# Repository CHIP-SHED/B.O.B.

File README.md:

Add battery power and LiPo charging to your Raspberry Pi projects.

======

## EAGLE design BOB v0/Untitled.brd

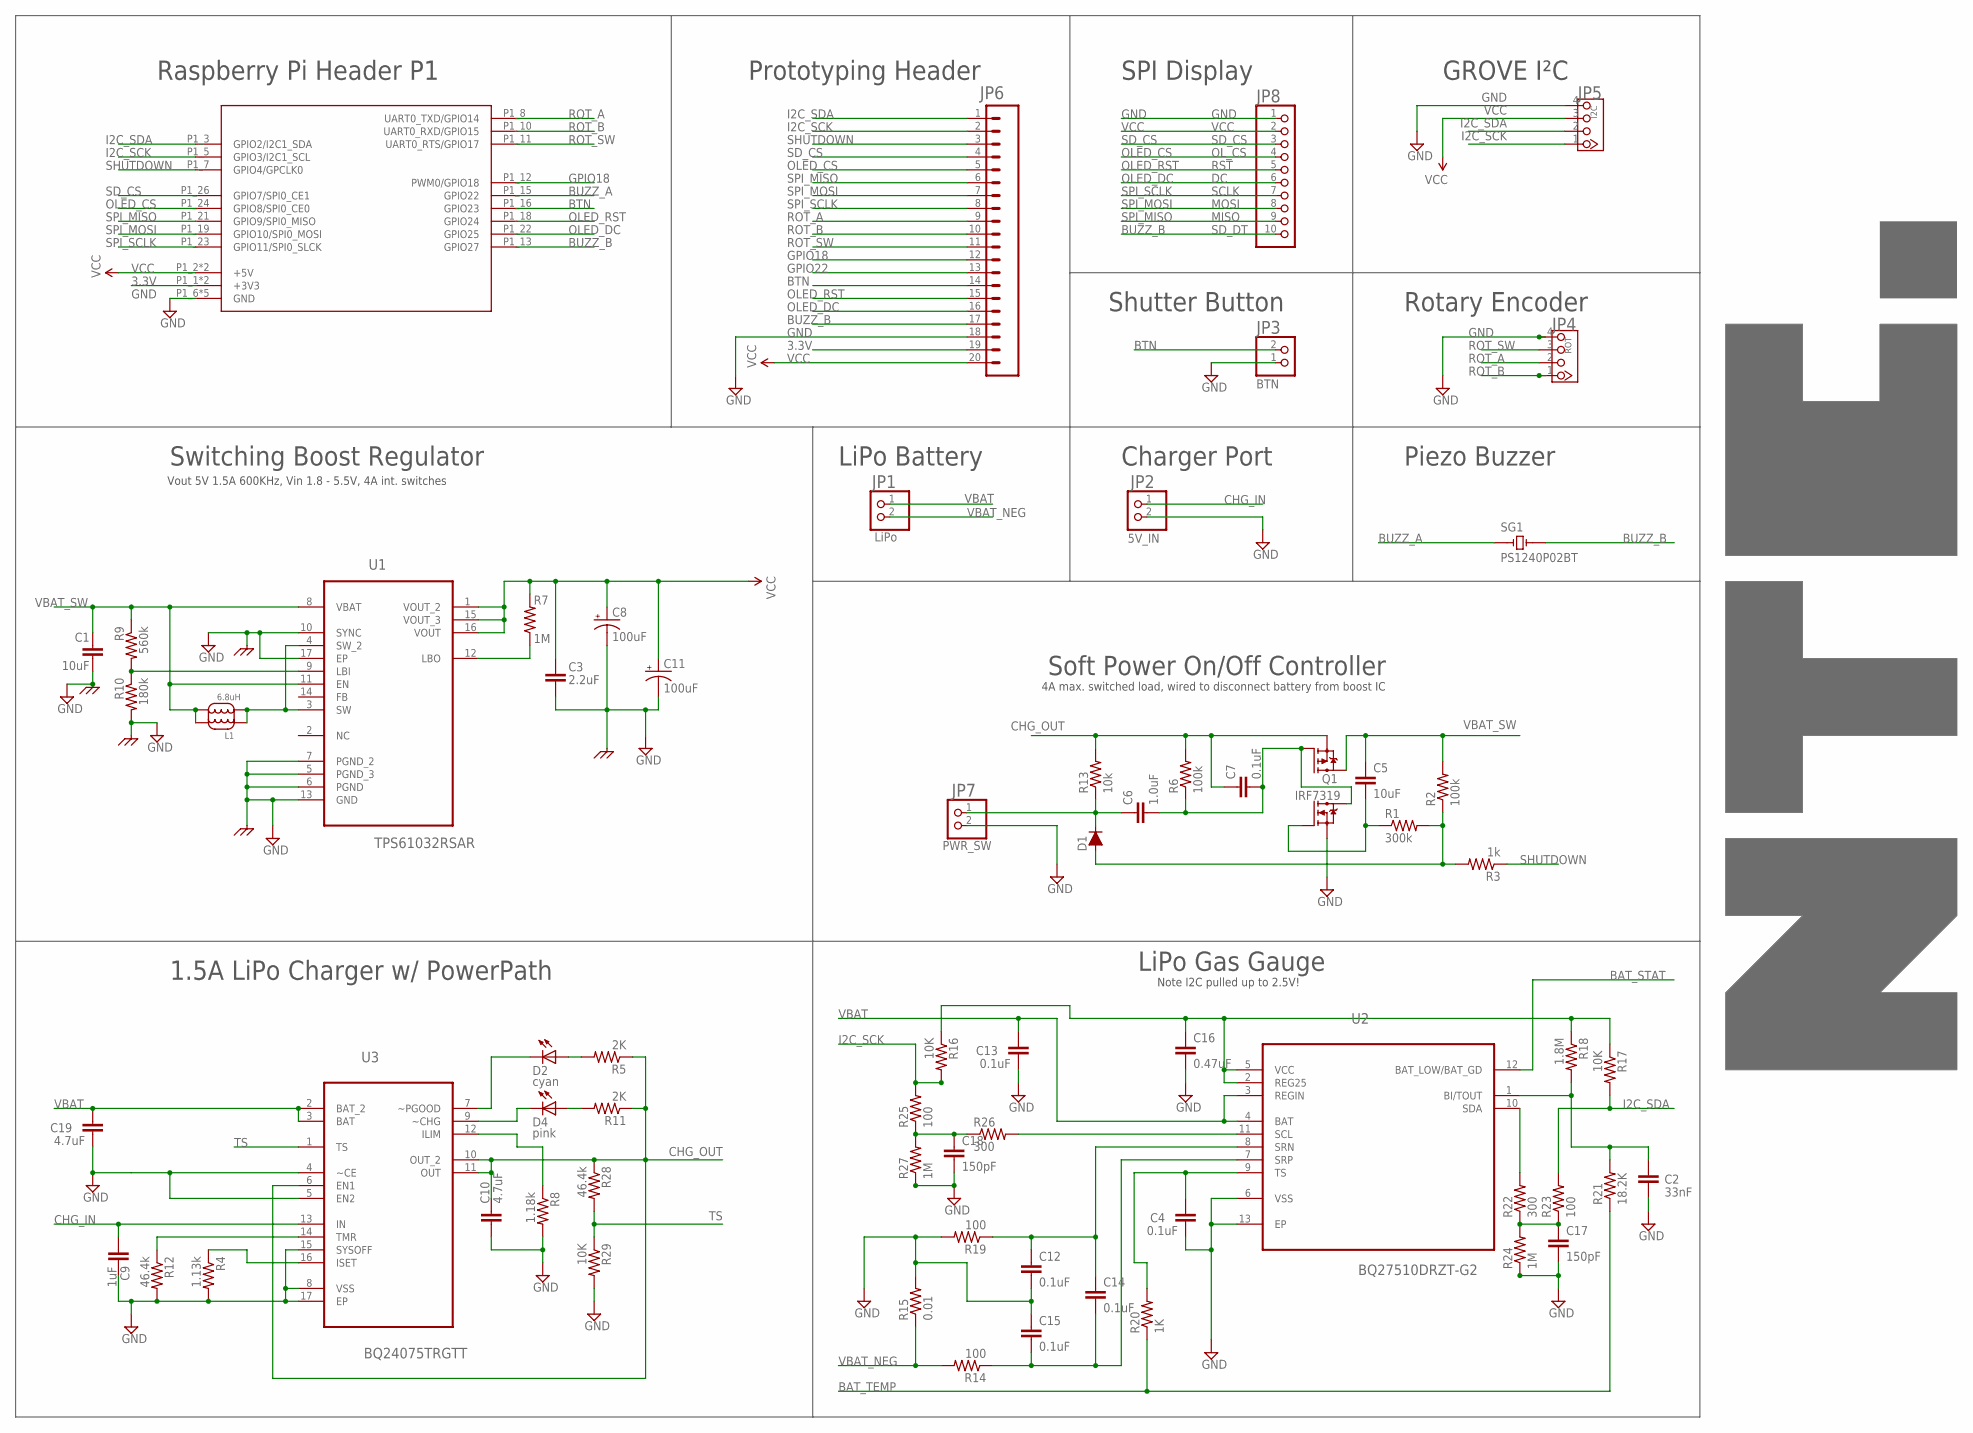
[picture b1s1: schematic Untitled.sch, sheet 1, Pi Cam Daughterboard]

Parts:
C1: 10uF; 1206
C2: 33nF; 0603-CAP
C3: 2.2uF; 0603
C4, C7, C12, C13, C14, C15: 0.1uF; 0603-CAP
C5: 10uF; 0603-CAP
C6: 1.0uF; 0603-CAP
C8, C11: 100uF; EIA3216
C9: 1uF; 0603-CAP
C10, C19: 4.7uF; 0603-CAP
C16: 0.47uF; 0603-CAP
C17, C18: 150pF; 0603-CAP
D1: D-FILL-SMB; SMB
D2: cyan; LED-0603
D4: pink; LED-0603
JP1: LiPo; JST-PH-2-THM-RA
JP2: 5V_IN; JST-PH-2-THM-RA
JP3: BTN; JST-PH-2-THM-RA
JP4: ROT; CONNECTOR_4P-2.0-90D
JP5: I2C; CONNECTOR_4P-2.0-90D
JP6: M20LOCK_LONGPADS; 1X20_LOCK_LONGPADS
JP7: PWR_SW; JST-PH-2-THM-RA
JP8: PINHD-1X10; 1X10-BIG
L1: 6.8uH; SUMIDA_CDRH124
PICAM_SHIELD: PICAM_RPI-B-PICAM
Q1: IRF7319; SO08-IRF
R1: 300k; 0603-RES
R2, R6: 100k; 0603-RES
R3: 1k; 0603-RES
R4: 1.13k; 0603-RES
R5, R11: 2K; 0603-RES
R7: 1M; 0603-RES
R8: 1.18k; 0603-RES
R9: 560k; 0603-RES
R10: 180k; 0603-RES
R12, R28: 46.4k; 0603-RES
R13: 10k; 0603-RES
R14, R19: 100; 0603-RES
R15: 0.01; SPARKFUN_1206
R16, R17, R29: 10K; 0603-RES
R18: 1.8M; 0603-RES
R20: 1K; SPARKFUN_1206
R21: 18.2K; SPARKFUN_1206
R22, R26: 300; SPARKFUN_1206
R23, R25: 100; SPARKFUN_1206
R24, R27: 1M; SPARKFUN_1206
SG1: PS1240P02BT; PS1240
U1: TPS61032RSAR; QFN65P400X400X100-17N
U2: BQ27510DRZT-G2; SON40P400X250X100-13N
U3: BQ24075TRGTT; QFN50P300X300X100-17N

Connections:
3.3V: JP6.19, PICAM_SHIELD.P1_1 (+3V3), PICAM_SHIELD.P1_17 (+3V3)
BAT_STAT: U2.12 (BAT_LOW/BAT_GD)
BAT_TEMP: R20.1, R21.1
BTN: JP3.2 (1), JP6.14, PICAM_SHIELD.P1_16 (GPIO23)
BUZZ_A: PICAM_SHIELD.P1_15 (GPIO22), SG1.P$1 (1)
BUZZ_B: JP6.17, JP8.10, PICAM_SHIELD.P1_13 (GPIO27), SG1.P$2 (2)
CHG_IN: C9.1, JP2.1 (2), U3.13 (IN)
CHG_OUT: C7.1, C10.1, Q1.3 (P-S2), R5.1, R6.2, R11.1, R13.2, R28.1, U3.6 (EN1), U3.10 (OUT_2), U3.11 (OUT)
GND: C1.2, C2.2, C3.2, C4.2, C8.C (-), C9.2, C10.2, C11.C (-), C12.2, C13.2, C15.1, C16.2, C17.2, C18.2, C19.2, JP2.2 (1), JP3.1 (2), JP4.4, JP5.4, JP6.18, JP7.2 (1), JP8.1, PICAM_SHIELD.P1_6 (GND), PICAM_SHIELD.P1_9 (GND), PICAM_SHIELD.P1_14 (GND), PICAM_SHIELD.P1_20 (GND), PICAM_SHIELD.P1_25 (GND), Q1.1 (N-S1), R4.2, R8.2, R10.2, R12.2, R15.2, R19.2, R24.1, R27.1, R29.2, U1.5 (PGND_3), U1.6 (PGND), U1.7 (PGND_2), U1.10 (SYNC), U1.13 (GND), U1.17 (EP), U2.6 (VSS), U2.13 (EP), U3.4 (~CE), U3.5 (EN2), U3.8 (VSS), U3.15 (SYSOFF), U3.17 (EP)
GPIO18: JP6.12, PICAM_SHIELD.P1_12 (PWM0/GPIO18)
GPIO22: JP6.13
I2C_SCK: JP5.1, JP6.2, PICAM_SHIELD.P1_5 (GPIO3/I2C1_SCL), R16.2, R25.2
I2C_SDA: JP5.2, JP6.1, PICAM_SHIELD.P1_3 (GPIO2/I2C1_SDA), R17.2, R23.2
L1: L1.P$3 (2), L1.P$4 (2), U1.3 (SW), U1.4 (SW_2)
unnamed: C6.1, D1.1 (C), JP7.1 (2), R13.1
unnamed: C2.1, R18.2, R21.2, U2.1 (BI/TOUT)
unnamed: C17.1, R22.1, R23.1, R24.2
unnamed: D4.C, U3.9 (~CHG)
unnamed: R7.1, U1.12 (LBO)
unnamed: R9.2, R10.1, U1.9 (LBI)
unnamed: R12.1, U3.14 (TMR)
unnamed: C5.2, Q1.2 (N-G1), R1.1
unnamed: R4.1, U3.16 (ISET)
unnamed: D4.A, R11.2
unnamed: D2.C, U3.7 (~PGOOD)
unnamed: D2.A, R5.2
unnamed: C6.2, C7.2, Q1.4 (P-G2), Q1.7 (N-D1), Q1.8 (N-D1), R6.1
unnamed: D1.2 (A), R1.2, R2.1, R3.2
unnamed: R22.2, U2.10 (SDA)
unnamed: C18.1, R25.1, R26.1, R27.2
unnamed: R8.1, U3.12 (ILIM)
unnamed: R26.2, U2.11 (SCL)
unnamed: C4.1, R20.2, U2.9 (TS)
unnamed: C16.1, R16.1, R17.1, R18.1, U2.2 (REG25), U2.5 (VCC)
OLED_CS: JP6.5, JP8.4, PICAM_SHIELD.P1_24 (GPIO8/SPI0_CE0)
OLED_DC: JP6.16, JP8.6, PICAM_SHIELD.P1_22 (GPIO25)
OLED_RST: JP6.15, JP8.5, PICAM_SHIELD.P1_18 (GPIO24)
ROT_A: JP4.2, JP6.9, PICAM_SHIELD.P1_8 (UART0_TXD/GPIO14)
ROT_B: JP4.1, JP6.10, PICAM_SHIELD.P1_10 (UART0_RXD/GPIO15)
ROT_SW: JP4.3, JP6.11, PICAM_SHIELD.P1_11 (UART0_RTS/GPIO17)
SD_CS: JP6.4, JP8.3, PICAM_SHIELD.P1_26 (GPIO7/SPI0_CE1)
SHUTDOWN: JP6.3, PICAM_SHIELD.P1_7 (GPIO4/GPCLK0), R3.1
SPI_MISO: JP6.6, JP8.9, PICAM_SHIELD.P1_21 (GPIO9/SPI0_MISO)
SPI_MOSI: JP6.7, JP8.8, PICAM_SHIELD.P1_19 (GPIO10/SPI0_MOSI)
SPI_SCLK: JP6.8, JP8.7, PICAM_SHIELD.P1_23 (GPIO11/SPI0_SLCK)
SRN: C12.1, C14.1, R19.1, U2.8 (SRN)
SRP: C14.2, C15.2, R14.1, U2.7 (SRP)
TS: R28.2, R29.1, U3.1 (TS)
VBAT: C13.1, C19.1, JP1.1 (2), U2.3 (REGIN), U2.4 (BAT), U3.2 (BAT_2), U3.3 (BAT)
VBAT_NEG: JP1.2 (1), R14.2, R15.1
VBAT_SW: C1.1, C5.1, L1.P$1 (1), L1.P$2 (1), Q1.5 (P-D2), Q1.6 (P-D2), R2.2, R9.1, U1.8 (VBAT), U1.11 (EN)
VCC: C3.1, C8.A (+), C11.A (+), JP5.3, JP6.20, JP8.2, PICAM_SHIELD.P1_2 (+5V), PICAM_SHIELD.P1_4 (+5V), R7.2, U1.1 (VOUT_2), U1.15 (VOUT_3), U1.16 (VOUT)

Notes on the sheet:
Switching Boost Regulator
1.5A LiPo Charger w/ PowerPath
Rotary Encoder
GROVE I²C
Shutter Button
Soft Power On/Off Controller
SPI Display
RST
OL_CS
SD_CS
VCC
GND
SCLK
MOSI
MISO
SD_DT
Prototyping Header
Raspberry Pi Header P1
LiPo Gas Gauge
4A max. switched load, wired to disconnect battery from boost IC
Vout 5V 1.5A 600KHz, Vin 1.8 - 5.5V, 4A int. switches
Piezo Buzzer
Charger Port
LiPo Battery
Note I2C pulled up to 2.5V!

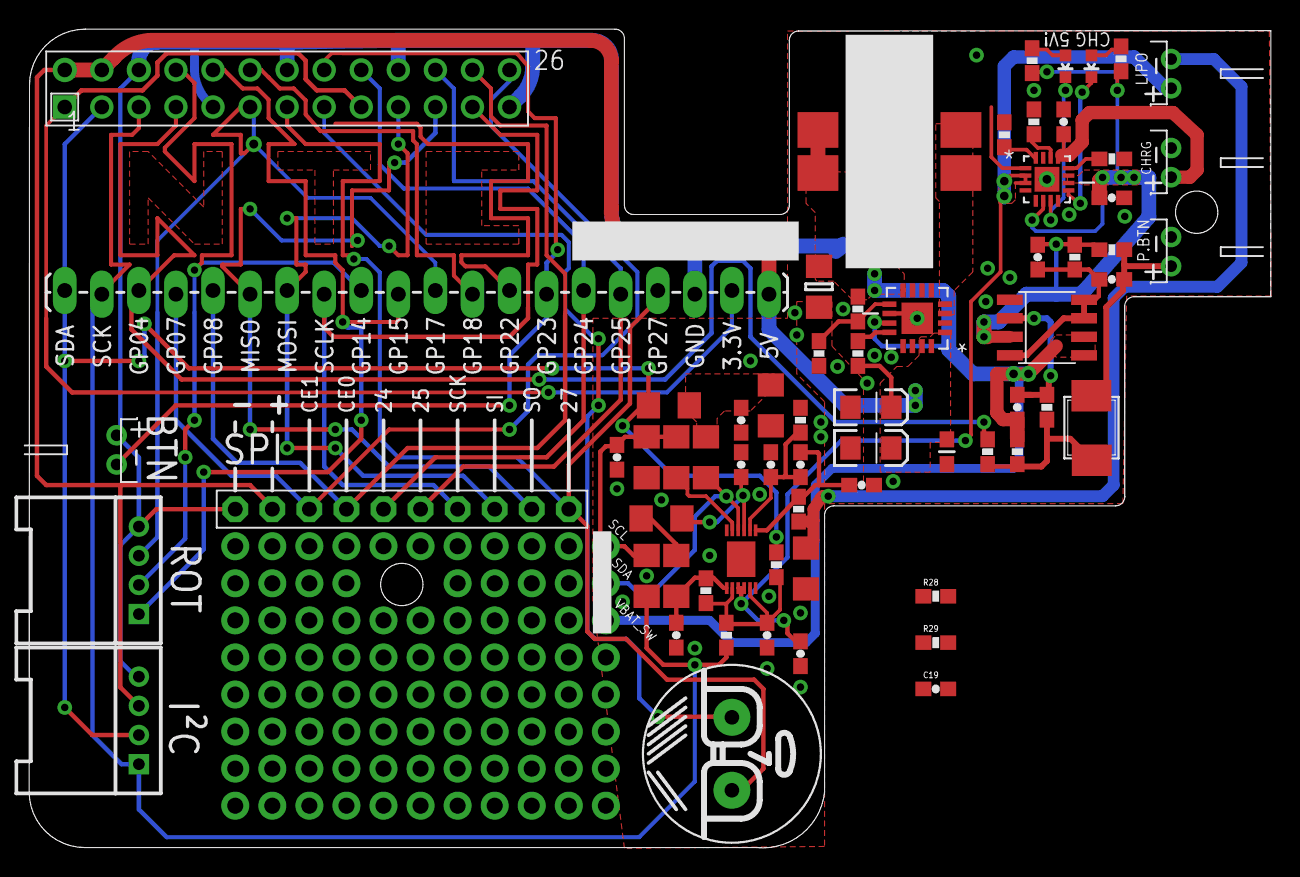
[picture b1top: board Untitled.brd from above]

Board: 2 copper layers, 85.1 x 56.1 mm, 66 parts (0 on the bottom side), 50 nets.

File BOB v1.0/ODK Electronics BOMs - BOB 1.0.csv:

QTY,Designator,Value,Device,Package,Mfg,Mfg P/N,Alt. Vendor Parts,Description,Datasheet
1,PCB,"1.6mm FR4, 1oz Copper, ENIG","White mask, Blue Silkscreen",,,,,,
1,C1,10uF,CAP1206-CAP,1206-CAP,Any/Generic,,,Min. 10V **X7R** Ceramic Capacitor,
2,"C10, C19",4.7uF,CAP0603-CAP,0603-CAP,Any/Generic,,,Min. 10V X5R Ceramic Capacitor,
1,C16,0.47uF,CAP0603-CAP,0603-CAP,Any/Generic,,,Min. 10V X5R Ceramic Capacitor,
0,"C17, C18",DNP,CAP0603-CAP,0603-CAP,Any/Generic,,,Min. 10V X5R Ceramic Capacitor,
1,C2,33nF,CAP0603-CAP,0603-CAP,Any/Generic,,,Min. 10V X5R Ceramic Capacitor,
1,C3,2.2uF,CAP0603-CAP,0603-CAP,Any/Generic,,,Min. 10V **X7R** Ceramic Capacitor,
7,"C4, C7, C12, C13, C14, C15, C20",0.1uF,CAP0603-CAP,0603-CAP,Any/Generic,,,Min. 10V X5R Ceramic Capacitor,
1,C5,10uF,CAP0603-CAP,0603-CAP,Any/Generic,,,Min. 10V X5R Ceramic Capacitor,
1,C6,1.0uF,CAP0603-CAP,0603-CAP,Any/Generic,,,Min. 10V X5R Ceramic Capacitor,
2,"C8, C11",220uF,CAP1210-CAP,1210-CAP,Any/Generic,,,Min. 10V **X7R** Ceramic Capacitor,
1,C9,1uF,CAP0603-CAP,0603-CAP,Any/Generic,,,Min. 10V X5R Ceramic Capacitor,
1,D1,,DIODE-SMB,SMB,Any/Generic,,Any/Generic,"Min. 16V, 3A Diode",
1,D2,"cyan or ""ice blue""",LED0603,0603-LED,Panasonic,LNJC36X8ARA1,Any/Generic (Cyan),Charge Complete LED,http://www.semicon.panasonic.co.jp/ds4/LNJC36X8ARA1_AEK_discon.pdf
1,D4,pink,LED0603,0603-LED,Panasonic,LNJP12X8ARA,Any/Generic (Pink),Charging Status LED,http://www.semicon.panasonic.co.jp/ds4/LNJP12X8ARA_E.pdf
1,J1,,"CONNECTOR_2x13_0.1"" VERT",PTH,Sullins,PPTC132LFBN-RC,Any/Generic,Raspberry Pi Pin Header,"http://www.sullinscorp.com/drawings/78_P(N)PxCxxxLFBN-RC,_10492-G.pdf"
4,"J6, J8, J9, J10",,CONNECTOR_JST_2PIN-THM VERT,PTH,JST,B2B-PH-K-S,Any/Generic,2.0mm 2 position JST Socket,http://www.jst-mfg.com/product/pdf/eng/ePH.pdf
2,"J5, J7",,CONNECTOR_TWIG-4P VERT,PTH,TE,440054-4,Any/Generic,"4 Pos Grove ""Twig"" Socket",http://www.te.com/commerce/DocumentDelivery/DDEController?Ac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
0,J2,DNP,CONNECTOR_M20LOCK_LONGPADS,DNP,DNP,,,"1x20 .100"" Pads",
0,J3,DNP,CONNECTOR_PINHD-1X10,DNP,DNP,,Any/Generic,"1x10 .100"" Header",
1,J4,,CONNECTOR_2.5mm_JST_EH_1x10 RA,PTH,JST,S10B-EH,Any/Generic,1x10 2.5mm Shrouded Header RA,http://www.jst-mfg.com/product/pdf/eng/eEH.pdf
1,L1,6.8uH,INDUCTOR-CDRH124NP-6R8MC,SMT CDRH124,Sumida,,"Wurth, EPCOS, Coilcraft",4.9A 6.8µH Inductor,http://www.sumida.com/products/pdf/CDRH124.pdf
1,Q1,IRF7319,IC-IRF7319,SO08-IRF,IR,IRF7319,Any/Generic,Dual N & P MOSFET IC,http://www.irf.com/product-info/datasheets/data/irf7319.pdf
1,R1,300K,RESISTOR0603-RES,0603-RES,Any/Generic,,Any/Generic,1/10W 5% Resistor,
1,R10,180K,RESISTOR0603-RES,0603-RES,Any/Generic,,Any/Generic,1/10W 5% Resistor,
2,"R12, R28",46.4K,RESISTOR0603-RES,0603-RES,Any/Generic,,Any/Generic,1/10W 5% Resistor,
2,"R13, R29",10K,RESISTOR0603-RES,0603-RES,Any/Generic,,Any/Generic,1/10W 5% Resistor,
0,"R16, R17",DNP,RESISTOR0603-RES,0603-RES,Any/Generic,,Any/Generic,1/10W 5% Resistor,
2,"R14, R19",100R,RESISTOR0603-RES,0603-RES,Any/Generic,,Any/Generic,1/10W 5% Resistor,
4,"R22, R23, R25, R26",0R,RESISTOR0603-RES,0603-RES,Any/Generic,,Any/Generic,1/10W 5% Resistor,
1,R15,0.01R,RESISTOR01206-RES,1206-RES,Any/Generic,,Any/Generic,1/10W **1%** Resistor,
1,R18,1.8M,RESISTOR0603-RES,0603-RES,Any/Generic,,Any/Generic,1/10W 5% Resistor,
2,"R2, R6",100K,RESISTOR0603-RES,0603-RES,Any/Generic,,Any/Generic,1/10W 5% Resistor,
1,R21,18.2K,RESISTOR0603-RES,0603-RES,Any/Generic,,Any/Generic,1/10W 5% Resistor,
2,"R3, R20",1K,RESISTOR0603-RES,0603-RES,Any/Generic,,Any/Generic,1/10W 5% Resistor,
1,R4,1.13K,RESISTOR0603-RES,0603-RES,Any/Generic,,Any/Generic,1/10W 5% Resistor,
2,"R5, R11",2K,RESISTOR0603-RES,0603-RES,Any/Generic,,Any/Generic,1/10W 5% Resistor,
1,R7,1M,RESISTOR0603-RES,0603-RES,Any/Generic,,Any/Generic,1/10W 5% Resistor,
2,"R24, R27",DNP,RESISTOR0603-RES,0603-RES,Any/Generic,,Any/Generic,1/10W 5% Resistor,
1,R8,1.18K,RESISTOR0603-RES,0603-RES,Any/Generic,,Any/Generic,1/10W 5% Resistor,
1,R9,560K,RESISTOR0603-RES,0603-RES,Any/Generic,,Any/Generic,1/10W 5% Resistor,
1,SG1,,DEVICE-PS1240P02BT,PTH 12.2mm OD,TDK,PS1240P02BT,Any/Generic,3V 70dB Sounder,http://product.tdk.com/en/catalog/datasheets/ef532_ps.pdf
0,SJ1,DNP,SOLDERJUMPER-CUTTABLETRACE,,N/A,,,,
0,"SJ2, SJ4",DNP,SOLDERJUMPER-2WY-1&2CONN,,N/A,,,,
0,"SJ3, SJ5",DNP,SOLDERJUMPER-2WY-2&3CONN,,N/A,,,,
1,U1,TPS61032RSAR,IC-TPS61032RSAR,QFN16,TI,TPS61032,PLS ADVISE OPTIONS,5V 1A DC-DC Boost IC,http://www.ti.com/product/tps61032
1,U2,BQ27510DRZT-G2,IC-BQ27510DRZT-G2,SON12,TI,BQ27510,PLS ADVISE OPTIONS,LiPo Gas Gauge IC,http://www.ti.com/lit/ds/symlink/bq27510-g2.pdf
1,U3,BQ24075TRGTT,IC-BQ24075TRGTT,VQFN16,TI,BQ24075,PLS ADVISE OPTIONS,1.5A LiPo Charger IC,http://www.ti.com/lit/ds/slus937a/slus937a.pdf

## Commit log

2014-11-20 all versions...
2014-11-20 add image and update gitignore
2014-11-20 Add board image to Readme

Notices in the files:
parts and their libraries:
SparkFun-Connectors: Licensing: CC v3.0 Share-Alike You are welcome to use this library for commercial purposes.
